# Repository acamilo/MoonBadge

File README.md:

# MoonBadge
Video of badge in use.

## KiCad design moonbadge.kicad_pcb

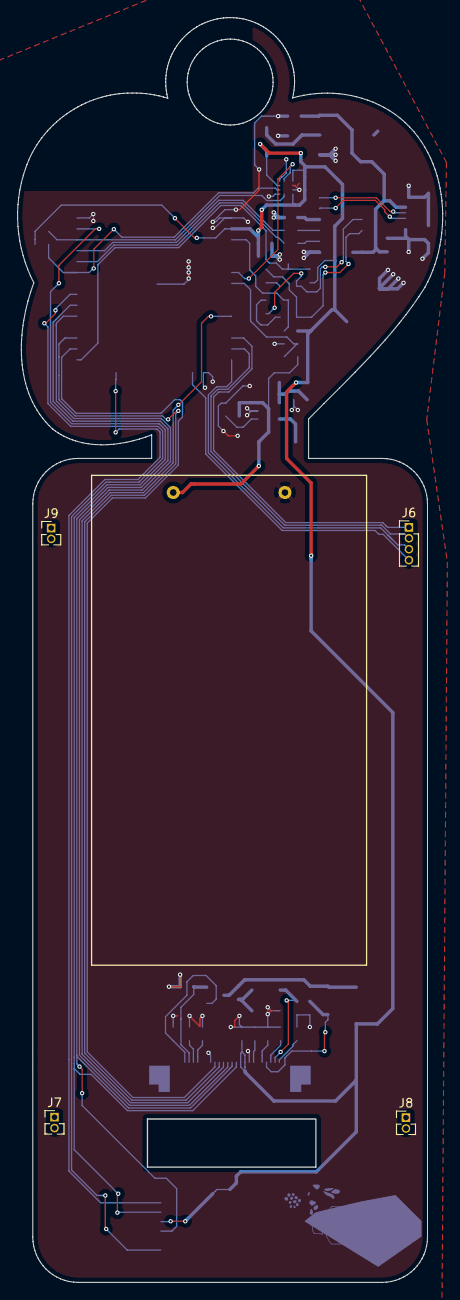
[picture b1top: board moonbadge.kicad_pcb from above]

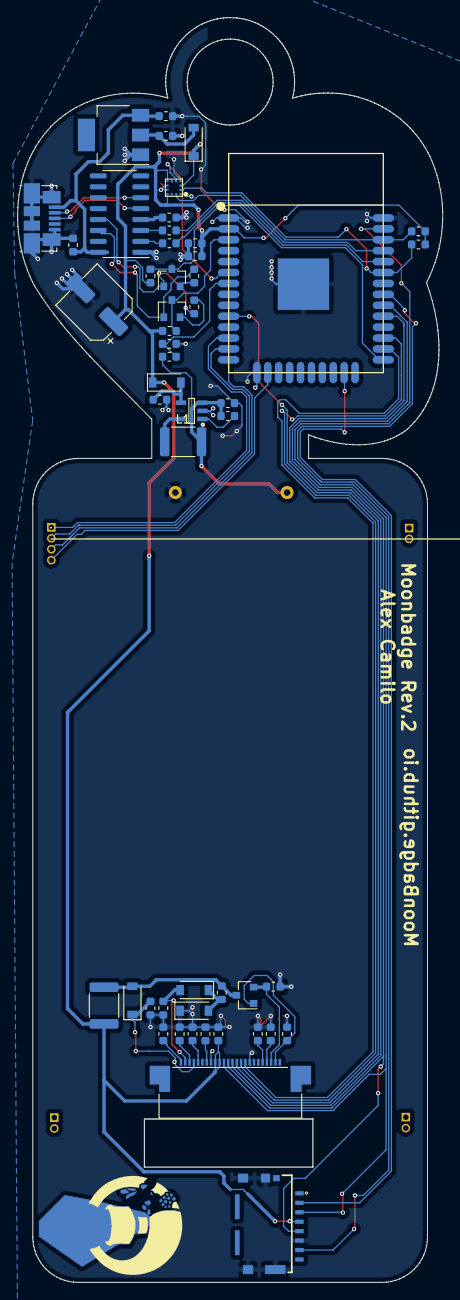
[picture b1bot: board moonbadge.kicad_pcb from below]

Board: 2 copper layers, 49.4 x 147.1 mm, 57 parts (51 on the bottom side), 49 nets.

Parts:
BT1: Battery_Cell; 12BH321P-GR
C1, C2, C3, C17: 10uF; C_0603_1608Metric
C4, C6, C7, C8, C9, C10, C11, C12, C13, C16, C18, C20: 1uF; C_0603_1608Metric
C5: 10uf; C_0603_1608Metric
C14: 2.2uF; C_0603_1608Metric
C19: 220uF; CP_Elec_6.3x5.7
D1, D2, D3, D4, D5: D_Schottky; D_SOD-123
J2: USB_B_Micro; USB_Micro-B_Molex_47346-0001
J6: Conn_01x04; PinHeader_1x04_P1.27mm_Vertical
J7, J8, J9: Conn_01x02; PinHeader_1x02_P1.27mm_Vertical
J10: 105162-0001
L1: L; L_1812_4532Metric
L2: 68uH; L_1812_4532Metric
Q1, Q3: PN2222A; SOT-23
Q2: Q_NMOS_GSD; SOT-23
R1: 10KR; C_0603_1608Metric
R2: DNP; C_0603_1608Metric
R3, R5, R6, R10: 10K; C_0603_1608Metric
R4: 2.2R; C_0603_1608Metric
R7, R9: 100k; C_0603_1608Metric
R8, R11: 1k; C_0603_1608Metric
R12, R13: 2.2k; C_0603_1608Metric
U1: ESP32-WROOM
U2: XC9141; SOT95P280X130-5N
U3: KX122-1037; LGA16R50P4X4_200X200X100
U4: AP1117-33; SOT-223-3_TabPin2
U5: CH340G; SOIC-16_3.9x9.9mm_P1.27mm
X1: 52435-2471; MOLEX_52435-2471
svg2mod: G***; tek-logo
svg2mod#2: G***; outline

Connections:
+3V3: C1.1, C4.1, C14.1, C19.1, D4.1, D5.1, J10.4, L2.2, R1.2, R3.1, R12.2, R13.1, U1.2, U3.3, U3.7, U3.10, X1.15, X1.16
+5V: C3.1, C18.2, J2.1, U4.3, U5.16
BAT: BT1.1, C2.1, L1.2, R2.2, R9.2, U2.3
BATSENSE: R7.2, R9.1, U1.7
DTR: Q1.1, R6.2, U5.13
EINK_BUSY: U1.26, X1.9
EINK_CS: U1.29, X1.12
EINK_DC: U1.10, X1.11
EINK_MOSI: J10.3, U1.37, X1.14
EINK_RESET: U1.27, X1.10
EINK_SCLK: J10.5, U1.30, X1.13
EN: Q3.3, R1.1, U1.3
GDR: Q2.1, R10.1, X1.2
GND: BT1.2, C1.2, C2.2, C3.2, C4.2, C5.2, C6.1, C7.1, C8.2, C9.2, C10.2, C11.2, C12.2, C14.2, C16.2, C17.2, C18.1, C19.2, C20.1, D3.1, J2.5, J2.6, J10.6, J10.10, J10.11, J10.12, J10.13, R4.2, R7.1, R10.2, U1.1, U1.15, U1.38, U1.39, U2.2, U3.1, U3.4, U3.8, U3.9, U4.1, U5.1, X1.8, X1.17
INT: U1.6, U3.5
IO0: Q1.3, R3.2, U1.25
MISO: J10.7, U1.31
MMC_CS: J10.2, U1.23
unnamed: C5.1, D5.2, U2.4
unnamed: C8.1, X1.18
unnamed: C9.1, X1.20
unnamed: C10.1, X1.22
unnamed: C11.1, X1.24
unnamed: C12.1, X1.5
unnamed: C13.1, D2.1, D3.2
unnamed: C13.2, D1.2, L2.1, Q2.3
unnamed: C16.1, X1.4
unnamed: C17.1, D4.2, U4.2
unnamed: C20.2, U5.4
unnamed: J2.2, U5.6
unnamed: J2.3, U5.5
unnamed: L1.1, U2.5
unnamed: Q1.2, R5.1
unnamed: Q3.2, R6.1
unnamed: R2.1, U2.1
unnamed: R8.2, U5.2
unnamed: R11.2, U5.3
RESE: Q2.2, R4.1, X1.3
RTS: Q3.1, R5.2, U5.14
RxD: R8.1, U1.34
SCL: R13.2, U1.36, U3.12
SDA: R12.1, U1.33, U3.2
T4: J6.4, U1.16
T5: J6.3, U1.14
T6: J6.2, U1.13
T7: J6.1, U1.12
TxD: R11.1, U1.35
VGH: C6.2, D1.1, X1.21
VGL: C7.2, D2.2, X1.23

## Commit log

2019-06-25 Board Graphics
2019-06-26 import assets from old badge and edit schematic
2019-06-26 Remove logos from old project
2019-06-27 board done.
2019-06-27 split boards into top and bottom
2019-06-27 removed extra copper pour
2019-06-27 removed extra pour
2019-06-27 removed designators, more cosmetic fixes
2019-06-27 more cosmetic updates. dont check in gerbers
2019-07-10 Added acrylic spacer
2019-07-10 Rev 2
    Swapped TX/RX
    Swapped battery polarity
    nudged battery down by 1mm to clear boost coil
2019-07-11 Added tek logo, removed files.
